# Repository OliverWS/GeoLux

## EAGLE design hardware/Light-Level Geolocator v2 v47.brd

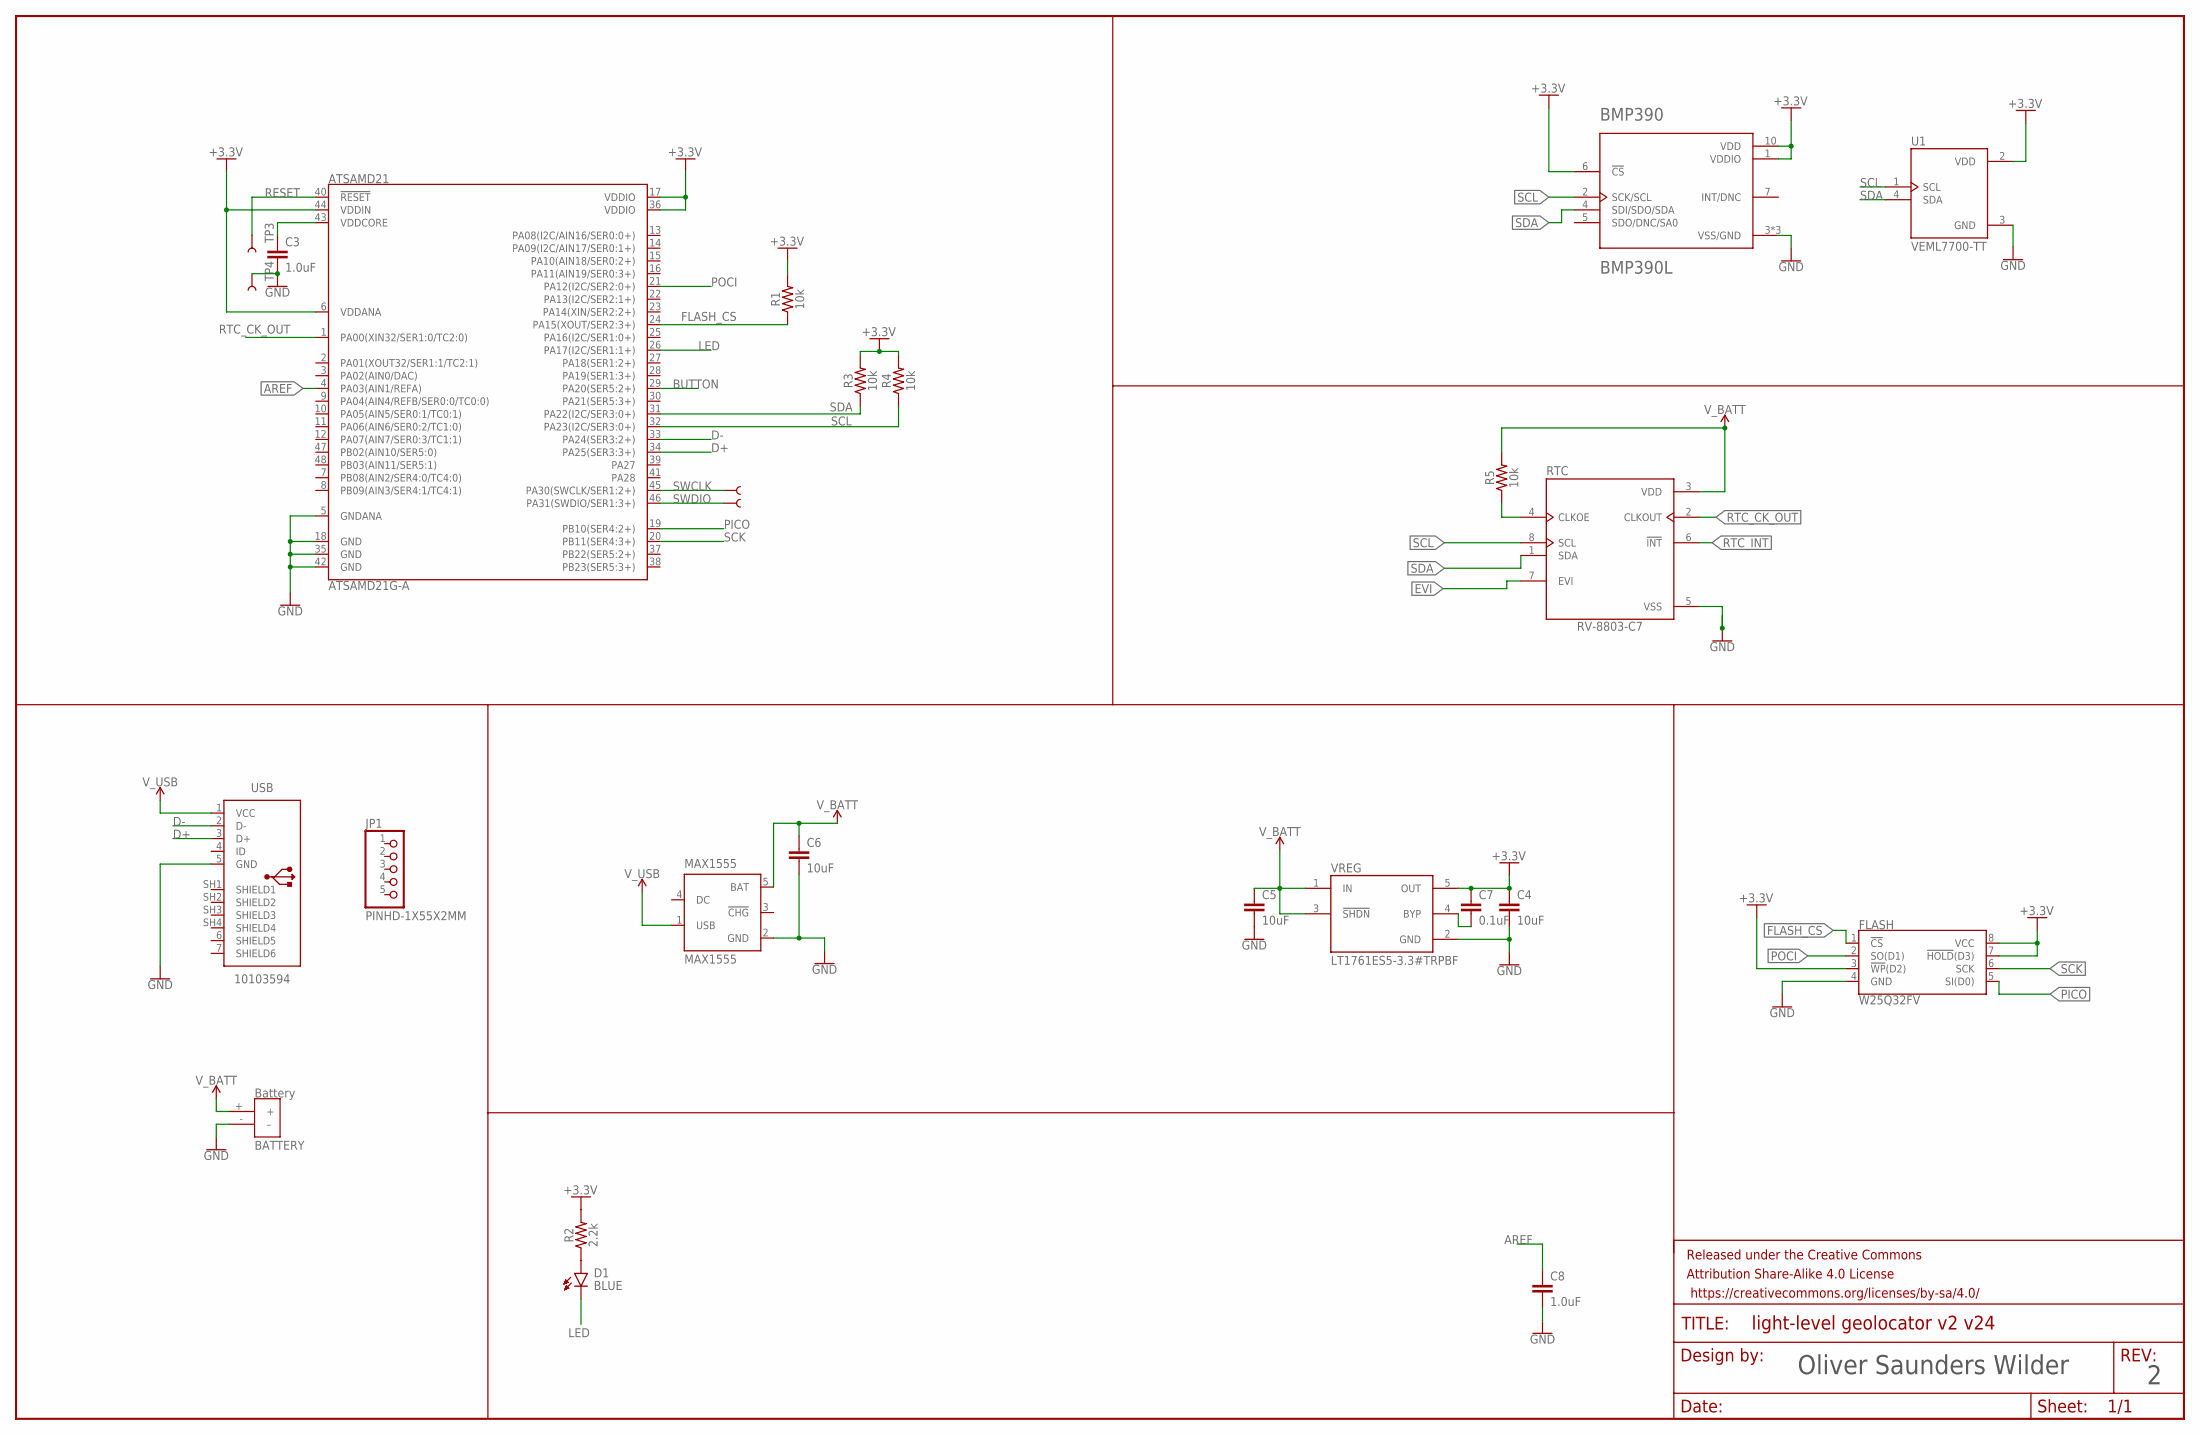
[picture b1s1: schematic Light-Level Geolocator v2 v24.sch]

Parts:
ATSAMD21: ATSAMD21G-A; TQFP-48
BMP390: BMP390L; XDCR_BMP390L
C3, C8: 1.0uF; 0603
C4, C5, C6: 10uF; 0603
C7: 0.1uF; 0603
D1: BLUE; LEDC1608X80N_FLAT-B
FLASH: W25Q32FV; SOIC-8
FRAME2: FRAME-LEDGER; CREATIVE_COMMONS
JP1: PINHD-1X55X2MM; 1_05X2MM
MAX1555: MAX1555; SOT23-5L
R1, R3, R4, R5: 10k; 0603
R2: 2.2k; 0603
RTC: RV-8803-C7; IC_RV-8803-C7_32.768KHZ_3PPM_TA_QC
TP1, TP2, TP3, TP4: TEST-POINT3; PAD.03X.03
U1: VEML7700-TT; XDCR_VEML7700-TT
U$1: BATTERY; BATT
USB: 10103594
VREG: LT1761ES5-3.3#TRPBF; SOT95P280X100-5N

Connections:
+3.3V: ATSAMD21.6 (VDDANA), ATSAMD21.17 (VDDIO), ATSAMD21.36 (VDDIO), ATSAMD21.44 (VDDIN), BMP390.1 (VDDIO), BMP390.6 (!CS), BMP390.10 (VDD), C4.1, C7.1, FLASH.3 (!WP!(D2)), FLASH.7 (!HOLD!(D3)), FLASH.8 (VCC), R1.2, R2.2, R3.2, R4.2, U1.2 (VDD), VREG.5 (OUT); also elsewhere on the board
AREF: ATSAMD21.4 (PA03(AIN1/REFA)), C8.1
BUTTON: ATSAMD21.29 (PA20(SER5:2+))
D+: ATSAMD21.34 (PA25(SER3:3+)), USB.3 (D+)
D-: ATSAMD21.33 (PA24(SER3:2+)), USB.2 (D-)
EVI: RTC.7 (EVI)
FLASH_CS: ATSAMD21.24 (PA15(XOUT/SER2:3+)), FLASH.1 (!CS!), R1.1
GND: ATSAMD21.5 (GNDANA), ATSAMD21.18 (GND), ATSAMD21.35 (GND), ATSAMD21.42 (GND), BMP390.3 (VSS/GND), BMP390.8 (VSS/GND), BMP390.9 (VSS/GND), C3.2, C4.2, C5.2, C6.2, C8.2, FLASH.4 (GND), MAX1555.2 (GND), RTC.5 (VSS), TP4.P$1, U1.3 (GND), U$1.- (–), USB.5 (GND), VREG.2 (GND); also elsewhere on the board
LED: ATSAMD21.26 (PA17(I2C/SER1:1+)), D1.C
unnamed: C7.2, VREG.4 (BYP)
unnamed: ATSAMD21.43 (VDDCORE), C3.1
unnamed: D1.A, R2.1
unnamed: R5.1, RTC.4 (CLKOE)
PICO: ATSAMD21.19 (PB10(SER4:2+)), FLASH.5 (SI(D0))
POCI: ATSAMD21.21 (PA12(I2C/SER2:0+)), FLASH.2 (SO(D1))
RESET: ATSAMD21.40 (!RESET!), TP3.P$1
RTC_CK_OUT: ATSAMD21.1 (PA00(XIN32/SER1:0/TC2:0)), RTC.2 (CLKOUT)
RTC_INT: RTC.6 (!INT)
SCK: ATSAMD21.20 (PB11(SER4:3+)), FLASH.6 (SCK)
SCL: ATSAMD21.32 (PA23(I2C/SER3:0+)), BMP390.2 (SCK/SCL), R4.1, RTC.8 (SCL), U1.1 (SCL); also elsewhere on the board
SDA: ATSAMD21.31 (PA22(I2C/SER3:0+)), BMP390.4 (SDI/SDO/SDA), R3.1, RTC.1 (SDA), U1.4 (SDA); also elsewhere on the board
SWCLK: ATSAMD21.45 (PA30(SWCLK/SER1:2+)), TP1.P$1
SWDIO: ATSAMD21.46 (PA31(SWDIO/SER1:3+)), TP2.P$1
V_BATT: C5.1, C6.1, MAX1555.5 (BAT), R5.2, RTC.3 (VDD), U$1.+, VREG.1 (IN), VREG.3 (!SHDN); also elsewhere on the board
V_USB: MAX1555.1 (USB), USB.1 (VCC)

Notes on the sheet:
Oliver Saunders Wilder

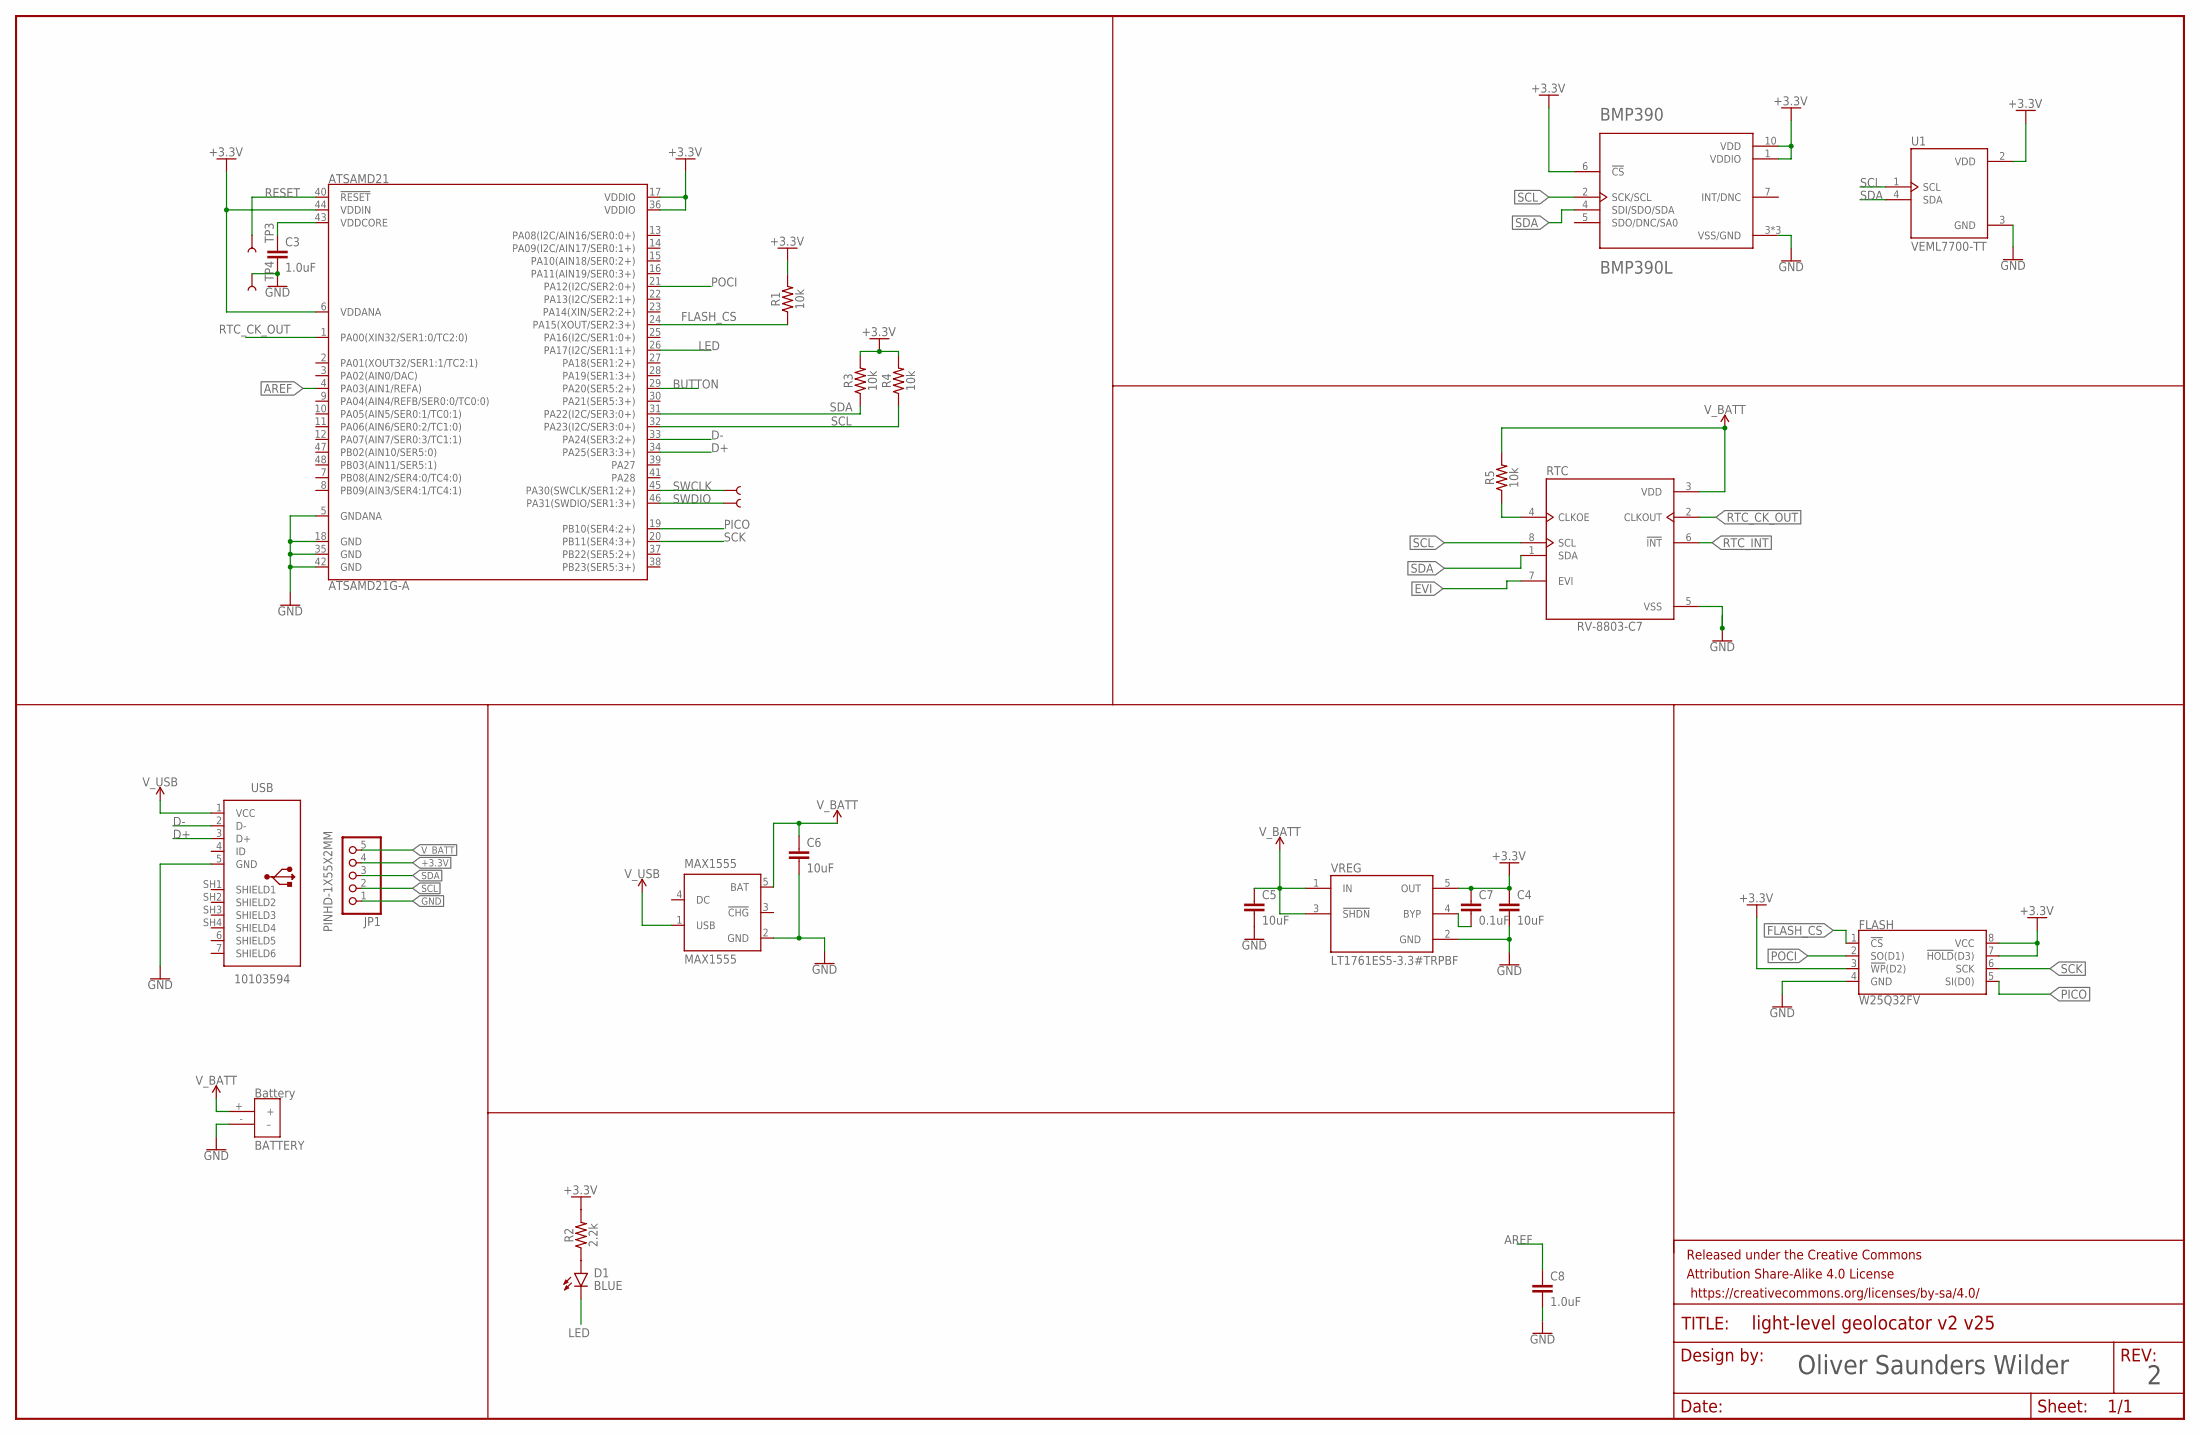
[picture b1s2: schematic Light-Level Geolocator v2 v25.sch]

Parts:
ATSAMD21: ATSAMD21G-A; TQFP-48
BMP390: BMP390L; XDCR_BMP390L
C3, C8: 1.0uF; 0603
C4, C5, C6: 10uF; 0603
C7: 0.1uF; 0603
D1: BLUE; LEDC1608X80N_FLAT-B
FLASH: W25Q32FV; SOIC-8
FRAME2: FRAME-LEDGER; CREATIVE_COMMONS
JP1: PINHD-1X55X2MM; 1_05X2MM
MAX1555: MAX1555; SOT23-5L
R1, R3, R4, R5: 10k; 0603
R2: 2.2k; 0603
RTC: RV-8803-C7; IC_RV-8803-C7_32.768KHZ_3PPM_TA_QC
TP1, TP2, TP3, TP4: TEST-POINT3; PAD.03X.03
U1: VEML7700-TT; XDCR_VEML7700-TT
U$1: BATTERY; BATT
USB: 10103594
VREG: LT1761ES5-3.3#TRPBF; SOT95P280X100-5N

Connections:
+3.3V: ATSAMD21.6 (VDDANA), ATSAMD21.17 (VDDIO), ATSAMD21.36 (VDDIO), ATSAMD21.44 (VDDIN), BMP390.1 (VDDIO), BMP390.6 (!CS), BMP390.10 (VDD), C4.1, C7.1, FLASH.3 (!WP!(D2)), FLASH.7 (!HOLD!(D3)), FLASH.8 (VCC), JP1.4, R1.2, R2.2, R3.2, R4.2, U1.2 (VDD), VREG.5 (OUT); also elsewhere on the board
AREF: ATSAMD21.4 (PA03(AIN1/REFA)), C8.1
BUTTON: ATSAMD21.29 (PA20(SER5:2+))
D+: ATSAMD21.34 (PA25(SER3:3+)), USB.3 (D+)
D-: ATSAMD21.33 (PA24(SER3:2+)), USB.2 (D-)
EVI: RTC.7 (EVI)
FLASH_CS: ATSAMD21.24 (PA15(XOUT/SER2:3+)), FLASH.1 (!CS!), R1.1
GND: ATSAMD21.5 (GNDANA), ATSAMD21.18 (GND), ATSAMD21.35 (GND), ATSAMD21.42 (GND), BMP390.3 (VSS/GND), BMP390.8 (VSS/GND), BMP390.9 (VSS/GND), C3.2, C4.2, C5.2, C6.2, C8.2, FLASH.4 (GND), JP1.1, MAX1555.2 (GND), RTC.5 (VSS), TP4.P$1, U1.3 (GND), U$1.- (–), USB.5 (GND), VREG.2 (GND); also elsewhere on the board
LED: ATSAMD21.26 (PA17(I2C/SER1:1+)), D1.C
unnamed: C7.2, VREG.4 (BYP)
unnamed: ATSAMD21.43 (VDDCORE), C3.1
unnamed: D1.A, R2.1
unnamed: R5.1, RTC.4 (CLKOE)
PICO: ATSAMD21.19 (PB10(SER4:2+)), FLASH.5 (SI(D0))
POCI: ATSAMD21.21 (PA12(I2C/SER2:0+)), FLASH.2 (SO(D1))
RESET: ATSAMD21.40 (!RESET!), TP3.P$1
RTC_CK_OUT: ATSAMD21.1 (PA00(XIN32/SER1:0/TC2:0)), RTC.2 (CLKOUT)
RTC_INT: RTC.6 (!INT)
SCK: ATSAMD21.20 (PB11(SER4:3+)), FLASH.6 (SCK)
SCL: ATSAMD21.32 (PA23(I2C/SER3:0+)), BMP390.2 (SCK/SCL), JP1.2, R4.1, RTC.8 (SCL), U1.1 (SCL); also elsewhere on the board
SDA: ATSAMD21.31 (PA22(I2C/SER3:0+)), BMP390.4 (SDI/SDO/SDA), JP1.3, R3.1, RTC.1 (SDA), U1.4 (SDA); also elsewhere on the board
SWCLK: ATSAMD21.45 (PA30(SWCLK/SER1:2+)), TP1.P$1
SWDIO: ATSAMD21.46 (PA31(SWDIO/SER1:3+)), TP2.P$1
V_BATT: C5.1, C6.1, JP1.5, MAX1555.5 (BAT), R5.2, RTC.3 (VDD), U$1.+, VREG.1 (IN), VREG.3 (!SHDN)
V_USB: MAX1555.1 (USB), USB.1 (VCC)

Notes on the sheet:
Oliver Saunders Wilder

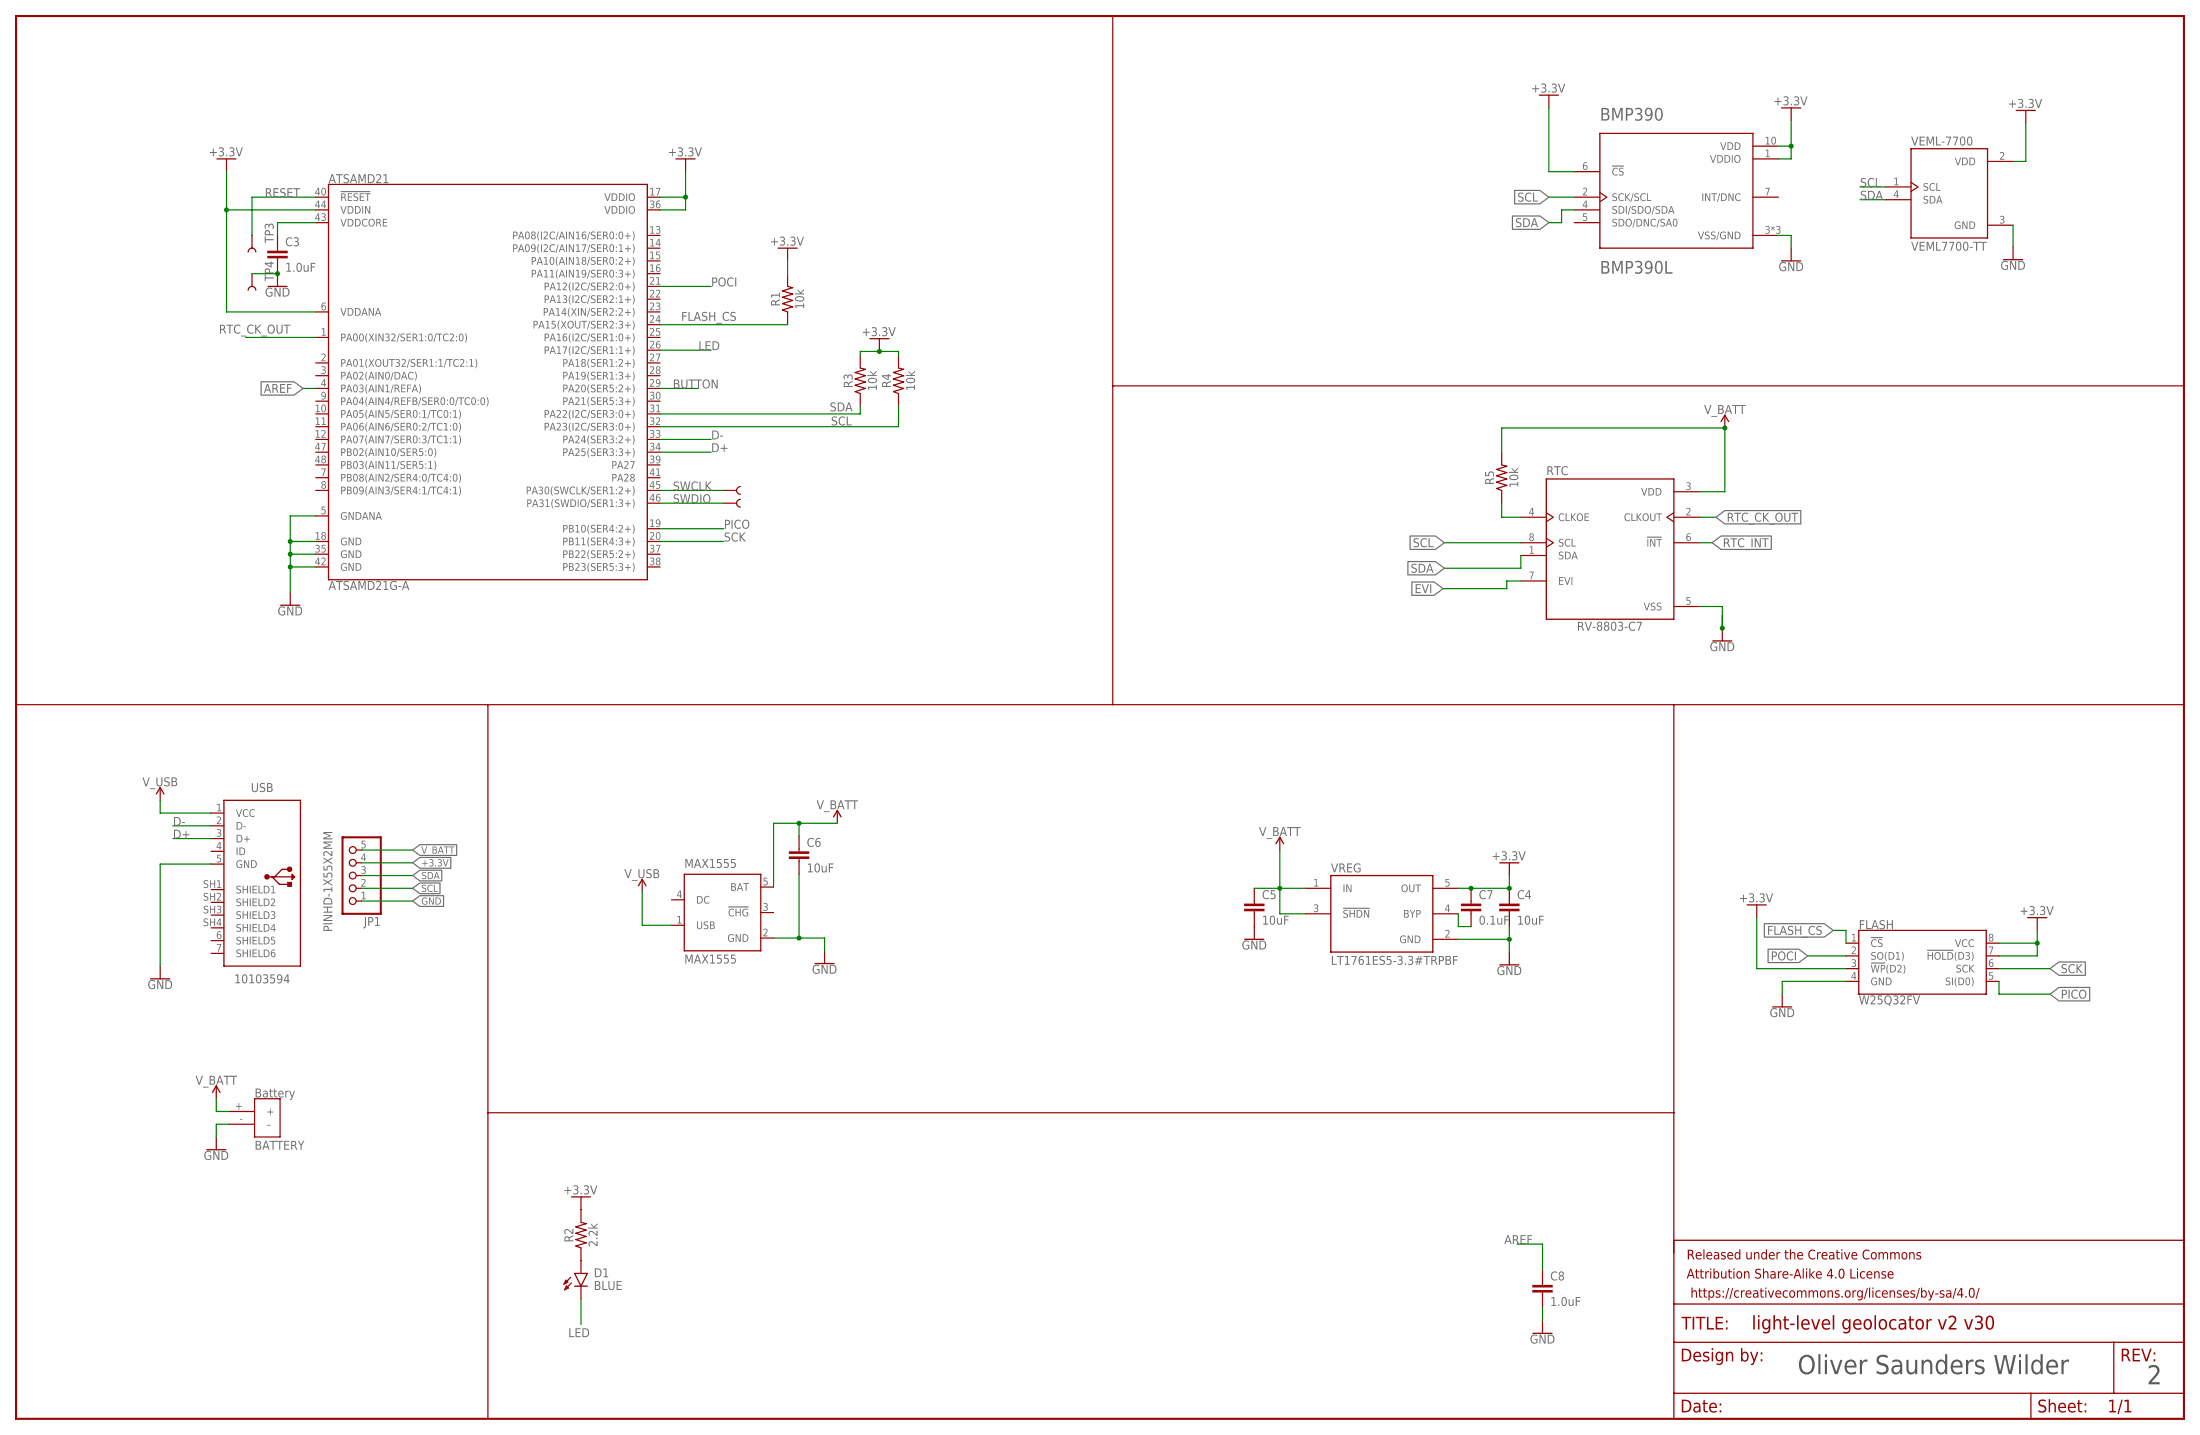
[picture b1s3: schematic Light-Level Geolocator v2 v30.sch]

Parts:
ATSAMD21: ATSAMD21G-A; TQFP-48
BMP390: BMP390L; XDCR_BMP390L
C3, C8: 1.0uF; 0603
C4, C5, C6: 10uF; 0603
C7: 0.1uF; 0603
D1: BLUE; LEDC1608X80N_FLAT-B
FLASH: W25Q32FV; SOIC-8
FRAME2: FRAME-LEDGER; CREATIVE_COMMONS
JP1: PINHD-1X55X2MM; 1_05X2MM
MAX1555: MAX1555; SOT23-5L
R1, R3, R4, R5: 10k; 0603
R2: 2.2k; 0603
RTC: RV-8803-C7; IC_RV-8803-C7_32.768KHZ_3PPM_TA_QC
TP1, TP2, TP3, TP4: TEST-POINT3; PAD.03X.03
U$1: BATTERY; BATT
USB: 10103594
VEML-7700: VEML7700-TT; XDCR_VEML7700-TT
VREG: LT1761ES5-3.3#TRPBF; SOT95P280X100-5N

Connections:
+3.3V: ATSAMD21.6 (VDDANA), ATSAMD21.17 (VDDIO), ATSAMD21.36 (VDDIO), ATSAMD21.44 (VDDIN), BMP390.1 (VDDIO), BMP390.6 (!CS), BMP390.10 (VDD), C4.1, C7.1, FLASH.3 (!WP!(D2)), FLASH.7 (!HOLD!(D3)), FLASH.8 (VCC), JP1.4, R1.2, R2.2, R3.2, R4.2, VEML-7700.2 (VDD), VREG.5 (OUT); also elsewhere on the board
AREF: ATSAMD21.4 (PA03(AIN1/REFA)), C8.1
BUTTON: ATSAMD21.29 (PA20(SER5:2+))
D+: ATSAMD21.34 (PA25(SER3:3+)), USB.3 (D+)
D-: ATSAMD21.33 (PA24(SER3:2+)), USB.2 (D-)
EVI: RTC.7 (EVI)
FLASH_CS: ATSAMD21.24 (PA15(XOUT/SER2:3+)), FLASH.1 (!CS!), R1.1
GND: ATSAMD21.5 (GNDANA), ATSAMD21.18 (GND), ATSAMD21.35 (GND), ATSAMD21.42 (GND), BMP390.3 (VSS/GND), BMP390.8 (VSS/GND), BMP390.9 (VSS/GND), C3.2, C4.2, C5.2, C6.2, C8.2, FLASH.4 (GND), JP1.1, MAX1555.2 (GND), RTC.5 (VSS), TP4.P$1, U$1.- (–), USB.5 (GND), VEML-7700.3 (GND), VREG.2 (GND); also elsewhere on the board
LED: ATSAMD21.26 (PA17(I2C/SER1:1+)), D1.C
unnamed: C7.2, VREG.4 (BYP)
unnamed: ATSAMD21.43 (VDDCORE), C3.1
unnamed: D1.A, R2.1
unnamed: R5.1, RTC.4 (CLKOE)
PICO: ATSAMD21.19 (PB10(SER4:2+)), FLASH.5 (SI(D0))
POCI: ATSAMD21.21 (PA12(I2C/SER2:0+)), FLASH.2 (SO(D1))
RESET: ATSAMD21.40 (!RESET!), TP3.P$1
RTC_CK_OUT: ATSAMD21.1 (PA00(XIN32/SER1:0/TC2:0)), RTC.2 (CLKOUT)
RTC_INT: RTC.6 (!INT)
SCK: ATSAMD21.20 (PB11(SER4:3+)), FLASH.6 (SCK)
SCL: ATSAMD21.32 (PA23(I2C/SER3:0+)), BMP390.2 (SCK/SCL), JP1.2, R4.1, RTC.8 (SCL), VEML-7700.1 (SCL); also elsewhere on the board
SDA: ATSAMD21.31 (PA22(I2C/SER3:0+)), BMP390.4 (SDI/SDO/SDA), JP1.3, R3.1, RTC.1 (SDA), VEML-7700.4 (SDA); also elsewhere on the board
SWCLK: ATSAMD21.45 (PA30(SWCLK/SER1:2+)), TP1.P$1
SWDIO: ATSAMD21.46 (PA31(SWDIO/SER1:3+)), TP2.P$1
V_BATT: C5.1, C6.1, JP1.5, MAX1555.5 (BAT), R5.2, RTC.3 (VDD), U$1.+, VREG.1 (IN), VREG.3 (!SHDN)
V_USB: MAX1555.1 (USB), USB.1 (VCC)

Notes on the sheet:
Oliver Saunders Wilder

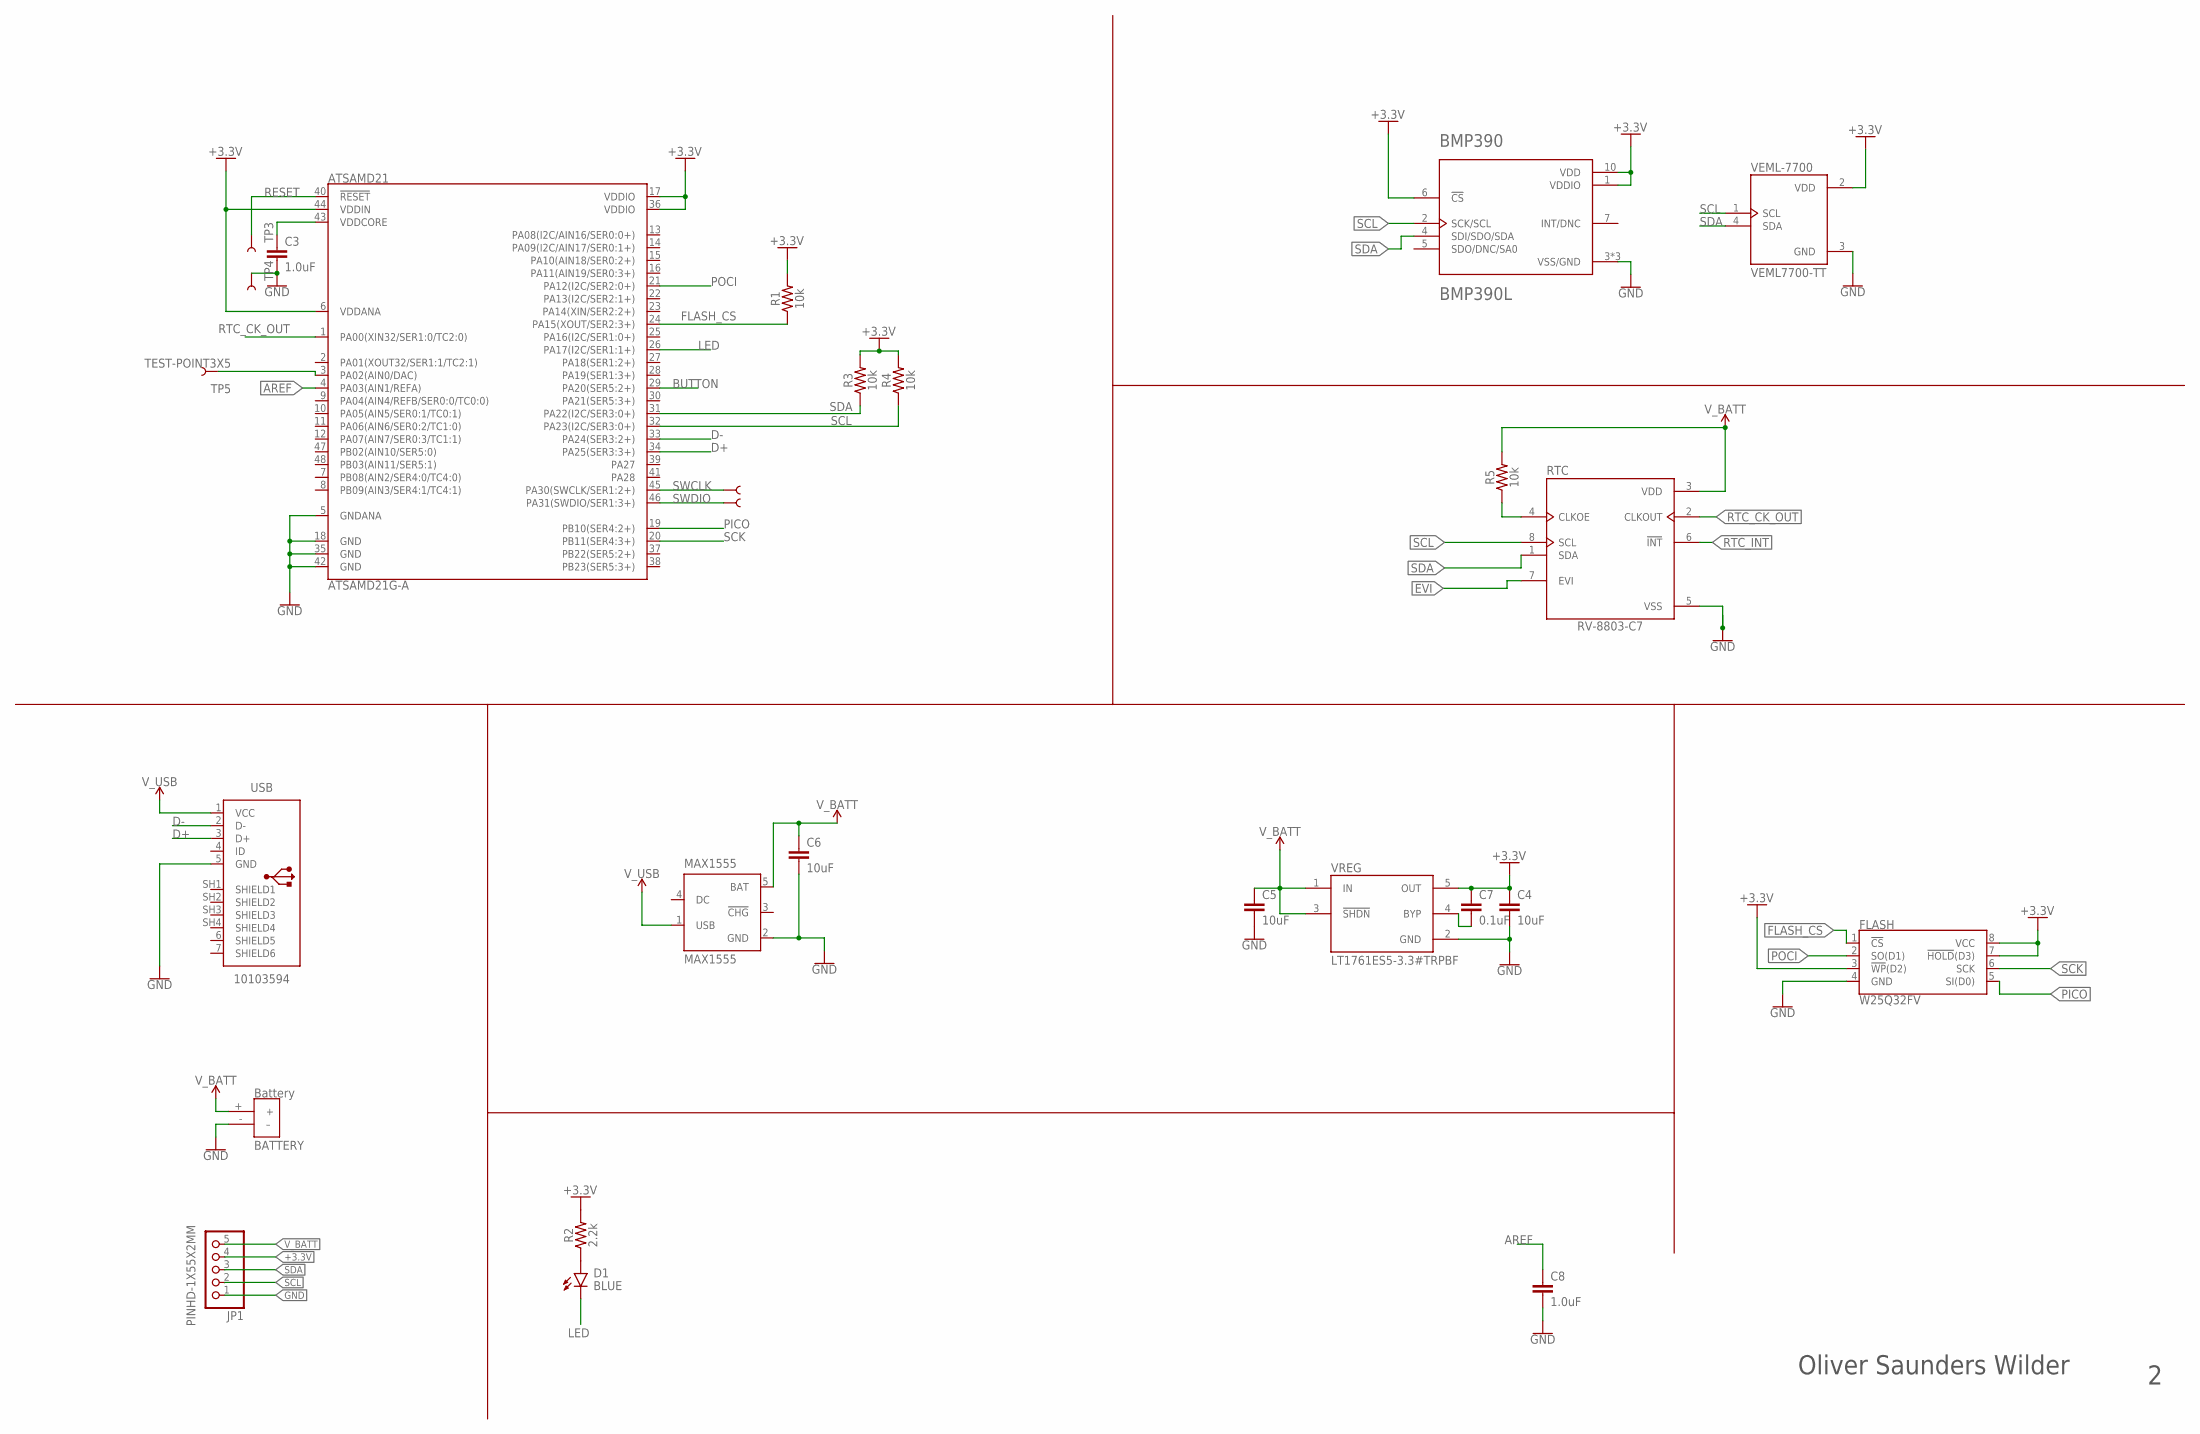
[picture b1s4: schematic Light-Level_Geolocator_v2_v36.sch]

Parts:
ATSAMD21: ATSAMD21G-A; TQFP-48
BMP390: BMP390L; XDCR_BMP390L
C3, C8: 1.0uF; 0603
C4, C5, C6: 10uF; 0603
C7: 0.1uF; 0603
D1: BLUE; LEDC1608X80N_FLAT-B
FLASH: W25Q32FV; SOIC-8
JP1: PINHD-1X55X2MM; 1_05X2MM
MAX1555: MAX1555; SOT23-5L
R1, R3, R4, R5: 10k; 0603
R2: 2.2k; 0603
RTC: RV-8803-C7; IC_RV-8803-C7_32.768KHZ_3PPM_TA_QC
TP1, TP2, TP3, TP4: TEST-POINT3; PAD.03X.03
TP5: TEST-POINT3X5; PAD.03X.05
U$1: BATTERY; BATT
USB: 10103594
VEML-7700: VEML7700-TT; XDCR_VEML7700-TT
VREG: LT1761ES5-3.3#TRPBF; SOT95P280X100-5N

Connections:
+3.3V: ATSAMD21.6 (VDDANA), ATSAMD21.17 (VDDIO), ATSAMD21.36 (VDDIO), ATSAMD21.44 (VDDIN), BMP390.1 (VDDIO), BMP390.6 (!CS), BMP390.10 (VDD), C4.1, C7.1, FLASH.3 (!WP!(D2)), FLASH.7 (!HOLD!(D3)), FLASH.8 (VCC), JP1.4, R1.2, R2.2, R3.2, R4.2, VEML-7700.2 (VDD), VREG.5 (OUT); also elsewhere on the board
AREF: ATSAMD21.4 (PA03(AIN1/REFA)), C8.1
BUTTON: ATSAMD21.29 (PA20(SER5:2+))
D+: ATSAMD21.34 (PA25(SER3:3+)), USB.3 (D+)
D-: ATSAMD21.33 (PA24(SER3:2+)), USB.2 (D-)
EVI: RTC.7 (EVI)
FLASH_CS: ATSAMD21.24 (PA15(XOUT/SER2:3+)), FLASH.1 (!CS!), R1.1
GND: ATSAMD21.5 (GNDANA), ATSAMD21.18 (GND), ATSAMD21.35 (GND), ATSAMD21.42 (GND), BMP390.3 (VSS/GND), BMP390.8 (VSS/GND), BMP390.9 (VSS/GND), C3.2, C4.2, C5.2, C6.2, C8.2, FLASH.4 (GND), JP1.1, MAX1555.2 (GND), RTC.5 (VSS), TP4.P$1, U$1.- (–), USB.5 (GND), VEML-7700.3 (GND), VREG.2 (GND); also elsewhere on the board
LED: ATSAMD21.26 (PA17(I2C/SER1:1+)), D1.C
unnamed: ATSAMD21.3 (PA02(AIN0/DAC)), TP5.P$1
unnamed: C7.2, VREG.4 (BYP)
unnamed: ATSAMD21.43 (VDDCORE), C3.1
unnamed: D1.A, R2.1
unnamed: R5.1, RTC.4 (CLKOE)
PICO: ATSAMD21.19 (PB10(SER4:2+)), FLASH.5 (SI(D0))
POCI: ATSAMD21.21 (PA12(I2C/SER2:0+)), FLASH.2 (SO(D1))
RESET: ATSAMD21.40 (!RESET!), TP3.P$1
RTC_CK_OUT: ATSAMD21.1 (PA00(XIN32/SER1:0/TC2:0)), RTC.2 (CLKOUT)
RTC_INT: RTC.6 (!INT)
SCK: ATSAMD21.20 (PB11(SER4:3+)), FLASH.6 (SCK)
SCL: ATSAMD21.32 (PA23(I2C/SER3:0+)), BMP390.2 (SCK/SCL), JP1.2, R4.1, RTC.8 (SCL), VEML-7700.1 (SCL); also elsewhere on the board
SDA: ATSAMD21.31 (PA22(I2C/SER3:0+)), BMP390.4 (SDI/SDO/SDA), JP1.3, R3.1, RTC.1 (SDA), VEML-7700.4 (SDA); also elsewhere on the board
SWCLK: ATSAMD21.45 (PA30(SWCLK/SER1:2+)), TP1.P$1
SWDIO: ATSAMD21.46 (PA31(SWDIO/SER1:3+)), TP2.P$1
V_BATT: C5.1, C6.1, JP1.5, MAX1555.5 (BAT), R5.2, RTC.3 (VDD), U$1.+, VREG.1 (IN), VREG.3 (!SHDN)
V_USB: MAX1555.1 (USB), USB.1 (VCC)

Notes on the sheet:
Oliver Saunders Wilder

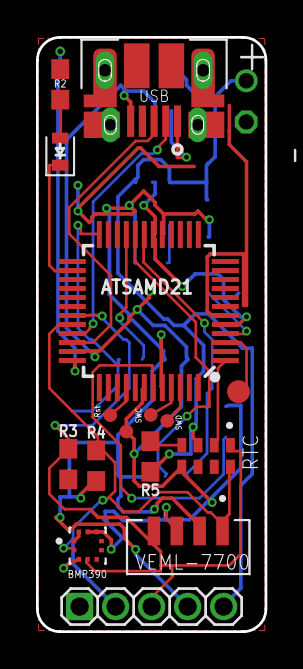
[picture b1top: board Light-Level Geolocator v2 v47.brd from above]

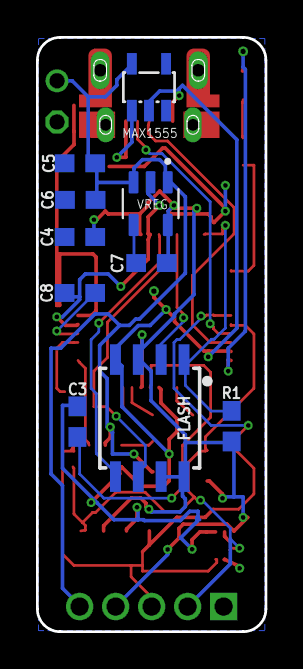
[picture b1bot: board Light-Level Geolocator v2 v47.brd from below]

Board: 2 copper layers, 12.7 x 33.0 mm, 27 parts (10 on the bottom side), 23 nets.

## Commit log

2023-04-22 Add initial code to test saving data to SPI FLASH chip
2023-05-01 Updates to let you configure key params via Serial
2023-05-12 Updates to code
2023-05-12 Add hardware
2023-05-12 Create v2 branch
2023-05-12 Adding hardware
2023-05-18 Refactor code to use FAT storage for data logging and config file
2023-05-18 Add push button reset
2023-05-19 Updated board design for v2
2023-05-31 Last version before v2
2023-06-01 Cleanup
2023-06-01 Fix gitignore to remove .DS_Store files

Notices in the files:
parts and their libraries:
SparkFun-IC-Microcontroller: Licensing: Creative Commons ShareAlike 4.0 International - https://creativecommons.org/licenses/by-sa/4.0
SparkFun-Aesthetics: Released under the Creative Commons Attribution Share-Alike 4.0 License
SparkFun-Aesthetics: https://creativecommons.org/licenses/by-sa/4.0
